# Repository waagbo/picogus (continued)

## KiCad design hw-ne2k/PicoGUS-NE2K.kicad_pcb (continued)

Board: 2 copper layers, 46 parts (0 on the bottom side), 94 nets, no tracks yet.

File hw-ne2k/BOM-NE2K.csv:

References,Qty,Value,Type,Footprint,Manufacturer,MPN,DigiKey PN,DigiKey link,DigiKey stock,Unit NOK (1 board),Line NOK (1 board),Alternatives,Notes
U1,1,Raspberry Pi Pico W,module (solder flat),RPi_PicoW_SMD_TH_USB,Raspberry Pi,SC0918,2648-SC0918CT-ND,https://www.digikey.no/no/products/result?keywords=2648-SC0918CT-ND,6986,72.90,72.90,Pico 2 W does NOT work (the NE2000 firmware is RP2040-only). Pico WH (pre-soldered headers) cannot be soldered flat.,Pico W (RP2040 + CYW43439 WiFi). Solder it FLAT (castellated edge or pins cut flush) so TP1-TP3 (USB) can be soldered from the back. Antenna end toward the bracket.
U2,1,74LVC244,SMD TSSOP-20,TSSOP-20_4.4x6.5mm_P0.65mm,Texas Instruments,SN74LVC244APW,296-26609-5-ND,https://www.digikey.no/no/products/result?keywords=296-26609-5-ND,2154,11.61,11.61,"Nexperia 74LVC244APW,118 (v1.2 BOM, DK 1727-2875-1-ND, 0 in stock today).","Octal buffer, 3V3, 5V-tolerant inputs"
"U3, U4",2,SN74CB3T3257,SMD TSSOP-16,TSSOP-16_4.4x5mm_P0.65mm,Texas Instruments,SN74CB3T3257PWR,296-17850-1-ND,https://www.digikey.no/no/products/result?keywords=296-17850-1-ND,4031,19.96,39.92,,TSSOP-16. No DIP or SOIC version exists (only PW/DGV).
U5,1,74AHC14,SMD SOIC-14,SOIC-14_3.9x8.7mm_P1.27mm,Diodes Inc,74AHC14S14-13,31-74AHC14S14-13CT-ND,https://www.digikey.no/no/products/result?keywords=31-74AHC1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,3070,3.55,3.55,,"Must be 74AHC14 (higher Schmitt threshold, see v1.2 changelog)."
U6,1,74LVC00,SMD SOIC-14,SOIC-14_3.9x8.7mm_P1.27mm,Diodes Inc,74LVC00AS14-13,31-74LVC00AS14-13CT-ND,https://www.digikey.no/no/products/result?keywords=31-74LVC0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,1816,3.65,3.65,,"Quad NAND, 3V3"
U7,1,74LVC1G00,SMD SOT-23-5,SOT-23-5,Texas Instruments,SN74LVC1G00DBVR,296-9845-1-ND,https://www.digikey.no/no/products/result?keywords=296-9845-1-ND,14500,1.34,1.34,,"Quad NAND, 3V3"
U8,1,APS6404L-3SQR-SN,SMD SOIC-8,SOIC-8_3.9x4.9mm_P1.27mm,AP Memory,APS6404L-3SQR-SN,1528-4677-ND,https://www.digikey.no/no/products/result?keywords=1528-4677-ND,4132,16.80,16.80,,SOIC-8. DigiKey does not stock the APS6404L itself; Adafruit 4677 is the DigiKey source (as in v1.2). Note: v1.2 BOM LCS
U10,1,74LVC2G06,SMD TSOP-6,TSOP-6_1.65x3.05mm_P0.95mm,Texas Instruments,SN74LVC2G06DBVR,296-13492-1-ND,https://www.digikey.no/no/products/result?keywords=296-13492-1-ND,25644,3.46,3.46,,"Open-drain inverters. U10A: IOCHRDY. U10B: unused (input driven by U5A, output open)."
U13,1,SST39SF010A,SMD PLCC-32,PLCC-32_11.4x14.0mm_P1.27mm,Microchip,SST39SF010A-70-4C-NHE,SST39SF010A-70-4C-NHE-ND,https://www.digikey.no/no/products/result?keywords=SST39SF01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,4137,18.87,18.87,,"Boot ROM: 128 KB 5 V flash = 4 banks of 32 KB, in-system writable from DOS (J2 fitted)"
U14,1,74HCT688,SMD SOIC-20W,SOIC-20W_7.5x12.8mm_P1.27mm,Texas Instruments,CD74HCT688M96,296-24357-1-ND,https://www.digikey.no/no/products/result?keywords=296-24357-1-ND,9672,7.43,7.43,,"Boot ROM address decoder (SA15-SA19 vs Pico-set base, enable)"
U15,1,74AHCT245,SMD TSSOP-20,TSSOP-20_4.4x6.5mm_P0.65mm,Texas Instruments,SN74AHCT245PWR,296-1118-1-ND,https://www.digikey.no/no/products/result?keywords=296-1118-1-ND,17137,7.72,7.72,,Boot ROM data buffer onto the ISA bus
U16,1,74AHCT1G08,SMD SOT-23-5,SOT-23-5,Texas Instruments,SN74AHCT1G08DBVR,296-1113-1-ND,https://www.digikey.no/no/products/result?keywords=296-1113-1-ND,66802,1.52,1.52,,~MEMSTB = ~SMEMR AND ~SMEMW (low during any memory cycle)
U17,1,USBLC6-2SC6,SMD SOT-23-6,SOT-23-6,STMicroelectronics,USBLC6-2SC6,497-5235-1-ND,https://www.digikey.no/no/products/result?keywords=497-5235-1-ND,144111,5.15,5.15,,USB ESD protection
D1,1,B5819W,SMD SOD-123,D_SOD-123,Slkor,B5819W,5399-B5819WCT-ND,https://www.digikey.no/no/products/result?keywords=5399-B5819WCT-ND,67294,2.69,2.69,,"1A 40V Schottky, DO-41"
F1,1,500mA PTC,SMD 1206,Fuse_1206_3216Metric,Bourns,MF-NSMF050-2,MF-NSMF050-2CT-ND,https://www.digikey.no/no/products/result?keywords=MF-NSMF05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,30039,3.81,3.81,,"USB VBUS polyfuse, 0.5 A hold"
"C1, C2",2,47uF,SMD 1206,C_1206_3216Metric,TDK,C3216X5R1A476M160AB,445-6006-1-ND,https://www.digikey.no/no/products/result?keywords=445-6006-1-ND,33669,7.97,15.94,v1.2 Samsung CL31A476MPHNNNE (0 at DigiKey today).,"47uF 35V aluminium electrolytic, 5mm dia, 2mm pitch"
"C3, C4, C5, C6, C7, C8, C9, C11, C12, C13, C14, C15, C17",13,0.1uF,SMD 0805,C_0805_2012Metric,Samsung,CL21B104KBCNNNC,1276-1003-1-ND,https://www.digikey.no/no/products/result?keywords=1276-1003-1-ND,4889645,0.43,5.59,,50V X7R.
C10,1,1uF,SMD 0805,C_0805_2012Metric,TDK,C2012X7R1H105K125AB,445-7547-1-ND,https://www.digikey.no/no/products/result?keywords=445-7547-1-ND,7594,2.88,2.88,,50V X7R.
C16,1,10uF,SMD 1206,C_1206_3216Metric,Samsung,CL31A106KAHNNNE,1276-1075-1-ND,https://www.digikey.no/no/products/result?keywords=1276-1075-1-ND,18634,2.11,2.11,"TDK C3216X5R1E106K160AB (DK 445-6862-1-ND, 43950).",USB VBUS bulk. 25V X5R. 1206 because no 10uF 0805 is in stock at DigiKey today.
R1,1,1k,SMD 0805,R_0805_2012Metric,Yageo,RC0805FR-071KL,311-1.00KCRCT-ND,https://www.digikey.no/no/products/result?keywords=311-1.00KCRCT-ND,732526,0.96,0.96,,1k 1/4W 1% metal film
"R2, R5, R6",3,15k,SMD 0805,R_0805_2012Metric,Yageo,RC0805FR-0715KL,311-15.0KCRCT-ND,https://www.digikey.no/no/products/result?keywords=311-15.0KCRCT-ND,127426,0.96,2.88,,15k 1/4W 1% metal film
"R3, R4",2,10k,SMD 0805,R_0805_2012Metric,Yageo,RC0805FR-0710KL,311-10.0KCRCT-ND,https://www.digikey.no/no/products/result?keywords=311-10.0KCRCT-ND,2120333,0.96,1.92,,10k 1/4W 1% metal film
J1,1,2x5 header,THT,PinHeader_2x05_P2.54mm_Vertical,Amphenol,10129381-910001BLF,10129381-910001BLF-ND,https://www.digikey.no/no/products/result?keywords=10129381-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,8685,6.96,6.96,,"IRQ select: one jumper (IRQ 2/9, 3, 4, 5 or 7)"
"J2, J6",2,1x2 header,THT,PinHeader_1x02_P2.54mm_Vertical,Amphenol,77311-118-02LF,609-4434-ND,https://www.digikey.no/no/products/result?keywords=609-4434-ND,56935,1.72,3.43,,J2: boot ROM write enable (fit the jumper only while flashing). J6: debug UART TX + GND. 30 uin gold.
J5,1,USB-A,THT,USB_A_Molex_67643_Horizontal,Molex,0676432910,WM11258-ND,https://www.digikey.no/no/products/result?keywords=WM11258-ND,894,18.20,18.20,"Wurth 614004134726 (DK 732-2731-ND, different footprint).","USB host port (mouse/joystick/storage), at the bracket below the antenna"
(jumpers),2,2.54mm jumper shunt,THT,,Harwin,M7582-05,952-2881-ND,https://www.digikey.no/no/products/result?keywords=952-2881-ND,,1.52,3.04,Blue: Harwin M7583-05 (DK 952-2882-ND). Red: Harwin M7581-05 (DK 952-2169-ND). Same open-top 2.54 mm shunt.,"One for J1 (IRQ), one for J2 (boot-ROM write enable: fit only while flashing the ROM)."
J3,0,,not fitted,,,,,,,,,,"ISA card edge (PCB gold fingers, order with chamfered/bevelled edge)"
H1,0,,not fitted,,,,,,,,,,Bracket mounting hole
H2,0,,not fitted,,,,,,,,,,Bracket mounting hole

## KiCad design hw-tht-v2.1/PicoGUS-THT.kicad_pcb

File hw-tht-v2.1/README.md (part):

# PicoGUS THT v2.1 – PicoGUS 2.0 in through hole, on a Waveshare Core2350B (RP2350B)

Board revision **v2.1**: the [PicoGUS 2.0](../hw-chipdown) circuit (chip-down RP2040, SMD) rebuilt for hand assembly
with through-hole parts. The RP2040, its flash, crystal and core regulator are replaced by a
**Waveshare Core2350B2** module (RP2350B, 16 MB flash, **8 MB PSRAM**) on four 2x8 sockets, and the module's PSRAM is
the GUS sample RAM, so v2.0's separate APS6404L is gone. Everything else is v2.0's circuit with the same GPIO map:
ISA bus logic, PCM5100A DAC, M62429 Waveblaster volume, MIDI out, USB-A host port and IRQ/DMA jumpers. The card is
the [THT v1.3.2](../hw-tht-v1.3.2/README.md) outline (102.0 × 99.95 mm), with v1.3.2's bracket-side connectors (USB-A,
line out, MIDI out) and bracket tab holes in v1.3.2's places, so the [v1.3.2 bracket](../hw-tht-v1.3.2/README.md#bracket) fits.
v2.0's passive line-out mix (four 1k resistors) is replaced by the **op-amp mixer of the THT v1.3 boards** (NE5532 on
ISA ±12 V, Waveblaster +6 dB), with film coupling capacitors and a DC-coupled DAC path.

The parts that only exist as SMD are soldered on the card: U1/U2 (SN74CB3T3257, TSSOP-16) and U10 (PCM5100A,
TSSOP-20) on THT v1.3.2's test-pad TSSOP footprints (hand-solder toes and a 0.7 mm test pad per pin), U13 (M62429L)
on v2.0's SOIC-8. Everything else is through hole; see
[Parts with no through-hole version](#parts-with-no-through-hole-version).

> **Status: schematic done; board placed and routed (4 layers, DRC clean, matches the schematic), for review. Not
> built or tested; no Gerbers yet. Firmware: ported and built (`picogus-v21.uf2`), not tested on hardware** (see
> [Firmware](#firmware) and [Layout status](#layout-status)).

Files:

| File | What |
|---|---|
| `PicoGUS-THT.kicad_pro/.kicad_sch/.kicad_pcb/.kicad_dru` | KiCad **10** project. Root sheet: v2.0's ISA logic, power, USB, Waveblaster and module |
| `audio.kicad_sch` | PCM5100A DAC sheet (v2.0's, footprints only) |
| `mixer.kicad_sch` | Line-out mixer: NE5532 inverting summing amplifier (from THT v1.3), ±12 V filters, Waveblaster input pull-downs |
| `PicoGUS-THT-schematic.pdf` | Schematic PDF |
| `BOM-THT.csv` | BOM with a **THT status** column (THT / THT but a different part than v2.0 / no THT version exists / module), the v2.0 part each line replaces, manufacturer, MPN, DigiKey and LCSC numbers, a digikey.no link, alternatives and digikey.no prices; then the kit items (module sockets and headers, jumpers), the optional IC sockets and the v2.0 parts that are gone |
| `BOM-THT-digikey-upload.csv` | DigiKey cart/BOM upload (see [Cost](#cost)). Customer Reference `PicoGUS-THT-2.1.x: <references>` on every line, so the bags of a mixed order say which board they are for; at most 48 characters (DigiKey prints "Character Limit Exceeded" instead of a longer one), so the 15 × 0.1 µF line reads `C2-7,14-16,20,…` |
| `BOM-THT-sockets.csv` (+ `-digikey-upload`) | Optional: every IC socketed, with socket and part heights against the Waveblaster daughterboard. The same parts are the optional socket lines of `BOM-THT.csv` |
| `BOM-THT-lcsc.csv`, `BOM-THT-lcsc-upload.csv`, `BOM-THT-sockets-lcsc-upload.csv` | The whole card from LCSC (see [Cost](#cost)): every BOM line with the LCSC part, order quantity (LCSC minimums), stock and price on the day and what to buy elsewhere; the uploads for LCSC's BOM tool, same customer references as the DigiKey ones |
| `tools/digikey_upload.py` | Writes both DigiKey upload files from `BOM-THT.csv` (`python3 tools/digikey_upload.py [cards]`; more than one card gives `-<n>x` files) |
| `tools/lcsc_bom.py` | Writes the three LCSC files from `BOM-THT.csv` with LCSC's live stock and prices (`python3 tools/lcsc_bom.py [cards]`) |
| `tools/gen_core2350b.py` | Generates the Core2350B footprint and 3D model in `hw-common` and checks the pin map |
| `PicoGUS-THT-top.png`, `PicoGUS-THT-bottom.png` | 3D renders |
| `docs/figures/routing.png` | The routed board: tracks per layer, vias and the AGND/AVDD islands |

The shared `PiGUS library` footprints are linked from `hw-common/`. **New in the shared library for v2.1:**
`Waveshare_Core2350B` (with a generated 3D model, `hw-common/parts/Waveshare_Core2350B.wrl`),
`USB_C_Receptacle_GCT_USB4085`, `TSSOP-16_4.4x5mm_P0.65mm_HandSolder_TestPads` and
`TSSOP-20_4.4x6.5mm_P0.65mm_HandSolder_TestPads` (THT v1.3.2's: KiCad's TSSOP with the toes to ±3.9 mm and one
0.7 mm round test pad per pin in two staggered columns per side, at x ±4.45 / ±5.1 mm),
`USB_A_Molex_67643_Horizontal_ShieldPin5` (KiCad's Molex 67643 with the shield pads
numbered 5, as the `USB_A` symbol's shield pin) and `DIP-8_W7.62mm_SOIC-8_Adapter` (no longer used here).

## What changed compared to v2.0

The schematic is v2.0's (`hw-chipdown`), upgraded to KiCad 10 and edited. Its netlist was compared with v2.0's
connection by connection: apart from the changes in this table the two are identical (119 multi-pin nets each).
Reference designators are v2.0's; new ones are D3, R19, R20 and C46.

| v2.0 | v2.1 | Why |
|---|---|---|
| U12 RP2040 (QFN-56), U11 W25Q128 flash, Y1 12 MHz crystal, R12/R14/R15/R16, C24–C37 (the RP2040 sheet) | **U12 Waveshare Core2350B** module on four 2x8 sockets (or soldered on its headers) | No chip-down RP2040 by hand. The module has the RP2350B, 16 MB flash, crystal, its own 3.3 V LDO and the 27 Ω USB resistors |
| U9 AMS1117-3.3 (SOT-223) | **U9 MCP1826S-3302E/AB** (TO-220) | Through hole, and 250 mV dropout: VSYS is now one Schottky drop below +5V (see [Power](#power)) |
| Q1 AO3401A ideal-diode switch (+5V → VSYS), R17 | **D3 1N5819** | No good TO-92 P-MOSFET; a second Schottky as for USB (D2) |
| J6 micro-USB (SMD) | **J6 GCT USB4085** through-hole USB-C + **R19/R20** 5.1 kΩ CC pull-downs | Through hole; device only, never sources VBUS |
| U6 74LVC2G06 (SOT-363), open-drain MIDI and I/O CH RDY drivers | **U6 74AHCT126** (DIP-14) on +5V + **C46** | No DIP open-drain inverter that runs on 3.3 V; the v1.3 THT boards' solution (OE = the old input, A tied low, so OE high pulls the line low). Spare gates tied low |
| U4/U5 74LVC00, U3 74AHC14, U7 SN74CB3T3245 (TSSOP) | 74AHC00 ×2, 74AHC14, **74AHC244** (DIP) | AHC: 3.3 V supply with 5 V tolerant inputs (as on v1.2/v1.3) |
| U1/U2 SN74CB3T3257, U10 PCM5100 (TSSOP) | same chips, **SMD on the card** (TSSOP-16/-20 on v1.3.2's hand-solder footprints with a test pad per pin) | No through-hole version exists |
| U8 APS6404L PSRAM (SOIC-8, GPIO0–3, PIO SPI) | **removed**: the Core2350B2's 8 MB PSRAM on the RP2350B's QMI (CS1 = GPIO47) | No through-hole PSRAM exists; the module's is memory mapped and faster. Needs the firmware port. GPIO0–3 are free |
| U13 M62429L (SOP-8) | same chip, **SMD on the card** (SOIC-8, v2.0's footprint) | The DIP-8 M62429P is not buyable |
| R6–R9 (1k passive mix), C43/C44 | **U11 NE5532 mixer** (sheet `mixer.kicad_sch`): R21–R32, C24–C29 | As THT v1.3: Waveblaster ×2 (+6 dB) and PCM ×1 summed, 100 Ω outputs, buffered line out |
| C39–C42 2.2 µF electrolytic (SMD) | **2.2 µF polyester film**, dual footprint (film on 5 mm, or a bipolar electrolytic on 2 mm) | Audio coupling: non-polar, low distortion |
| 0402/0603/0805/1206 R/C, CP_Elec_4x5.4, SOD-323, 0603 LED, 1206 PTC, 0805 beads, TL3305 switch, JST-SH debug | axial resistors and beads, radial MLCC discs and electrolytics, DO-41, 3 mm LED, radial PTC, 6 mm tactile switch, 1x3 header | Through hole |
| C11 47 µF (+3V3) | C11 10 µF | MCP1826S: at most 22 µF on its output |
| C38 100 µF ceramic | C38 100 µF electrolytic | Through hole |
| Card outline 102.87 × 96.74 mm, v2.0 bracket | **THT v1.3.2's outline** (102.0 × 99.95 mm) and bracket: J7 (MIDI out, top), J9 (line out) and J5 (USB-A, now v1.3.2's **Molex 67643**), H1/H2 and the ISA fingers at v1.3.2's positions | Reuses the v1.3.2 bracket; the 102 mm card is v1.3.2's cheaper JLCPCB size. The bracket's volume-pot hole is unused (v2.1's Waveblaster volume is digital) |
| 4 layers: In1 GND + AGND, In2 +3V3 + AVDD | 4 layers: In1.Cu GND plane + AGND island, In2.Cu +3V3 plane + AVDD island, under the audio section | As v2.0 |
| `+3.3V` power symbols | `+3V3` | The RP2040 sheet joined the two names; without it they would have split |

Unchanged references: J1 (ISA), J3 (IRQ/DMA), J7 (MIDI out), J8 (Waveblaster), J9 (line out), H1/H2, and every
GPIO assignment except GPIO0–3 (PSRAM, now free). Board positions: see [Layout status](#layout-status).

## Parts with no through-hole version

These are the v2.0 parts that cannot be replaced by a through-hole part. Everything else on v2.0 has a DIP, TO-220,
axial or radial equivalent (`THT status` column of `BOM-THT.csv`).

| v2.0 part | Package | Why there is no THT replacement | v2.1 |
|---|---|---|---|
| **RP2040** (+ W25Q128 flash, 12 MHz crystal) | QFN-56, SOIC-8, 3225 | No THT microcontroller of this class | **Waveshare Core2350B2 module** (RP2350B QFN-80 + 16 MB flash + crystal + 8 MB PSRAM) on four 2x8 headers |
| **APS6404L** 8 MB PSRAM | SOIC-8 | No THT PSRAM; the largest DIP SRAM (23LC1024) is 128 KB, a GUS needs 1 MB | **On the module**: the Core2350B2's PSRAM (firmware port needed) |
| **SN74CB3T3257** ×2 (5 V tolerant bus switches) | TSSOP-16 (no DIP/SOIC) | TI makes it in TSSOP/SSOP/TVSOP/VQFN only; the ISA interface needs it | Same chip, **SMD on the card** (TSSOP-16, 0.65 mm pitch) |
| **PCM5100A** DAC | TSSOP-20 only | The whole PCM510x family is TSSOP-20 | Same chip, **SMD on the card** (TSSOP-20, 0.65 mm pitch) |
| **M62429** volume control | SOP-8 (DIP-8 M62429P discontinued) | No DIP part in stock at DigiKey or LCSC; DIP clones (FM62429, U2429) only at hobby shops | Same chip, **SMD on the card** (SOIC-8, 1.27 mm pitch) |
| micro-USB receptacle | SMD | – | **GCT USB4085** through-hole USB-C: through hole, but 0.85 mm contact pitch (the hardest joint on the card) |

Replaced by a different through-hole part (circuit change): 74LVC2G06 → **74AHCT126** (U6), AO3401A → **1N5819**
(D3), AMS1117 → **MCP1826S** (U9), 74LVC00 → 74AHC00, SN74CB3T3245/74LVC244 → 74AHC244.

## Cost

digikey.no prices of 2026-10-30, for one board, in NOK; shipping not included. Per-line prices are in `BOM-THT.csv`.

| | NOK excl. MVA | NOK incl. 25 % MVA |
|---|---|---|
| DigiKey order, `BOM-THT-digikey-upload.csv` (43 lines) | 580.00 | 725.00 |
| Optional IC sockets, `BOM-THT-sockets-digikey-upload.csv` (U3–U7, U11) | 58.98 | 73.72 |
| Both | 638.98 | 798.73 |

* **Not in the DigiKey order**: the Core2350B2 (waveshare.com, US$6.99) and the M62429L (LCSC C52260216, minimum 5),
  and the PCB.
* J5 is now v1.3.2's Molex 67643 (DK WM4993-ND, 16.58 NOK, price of 2026-10-31), so it is in the DigiKey order.
* **C39–C42** (2.2 µF film, 61 NOK) are on backorder at DigiKey until about April 2027: see the LCSC film part or the
  bipolar electrolytic in [Audio](#audio).

**LCSC instead** (lcsc.com prices and stock of 2026-11-06, US$, shipping not included; `BOM-THT-lcsc.csv` has every
line):

| | US$ |
|---|---|
| LCSC order, `BOM-THT-lcsc-upload.csv` (40 lines, quantities raised to LCSC's minimums) | 50.93 |
| Optional IC sockets, `BOM-THT-sockets-lcsc-upload.csv` | 7.24 |

* **Not at LCSC**: U3 SN74AHC14N, U6 SN74AHCT126N and U9 MCP1826S-3302E/AB (none in stock, and no LCSC part fits
  without a design change: the 74HC14 does not take 5 V inputs at 3.3 V, the 125 has the opposite enable, the
  LM2940 clones want a larger output capacitor with ESR): buy them at DigiKey (296-4550-5-ND, 296-4659-5-ND,
  MCP1826S-3302E/AB-ND, about 30 NOK). The Core2350B2 comes from Waveshare.
* **Different parts from the BOM** (all in the `Note` column): U7 is TI's SN74LVC244AN (same pinout, 5 V-tolerant
  inputs at 3.3 V like the AHC244, stronger outputs), J7/J9 the XKB clones of the CUI jacks (as on THT v1.3.2),
  C21/C22 Dersonic C0G discs, R27/R28 and R31/R32 the taped Yageo MFR-25, and the generic headers, sockets,
  ferrites, film and electrolytic capacitors named in `BOM-THT.csv`.
* U4/U5 (SN74AHC00N): 60 in stock at LCSC on the day, at US$1.46 each.

## Audio

* **DAC**: PCM5100A (U10) as v2.0, output RC filter R10/R11 470 Ω + **C0G** C21/C22 2.2 nF (polypropylene film
  WIMA FKP2 is the alternative). Charge pump and decoupling MLCCs per the TI datasheet (X7R).
* **Waveblaster volume**: M62429L (U13) on AVDD as v2.0, inputs pulled to AGND by 100k (R31/R32, as THT v1.3),
  **film** coupling capacitors in and out (C39–C42).
* **Mixer** (`mixer.kicad_sch`, THT v1.3's): U11 NE5532 inverting summing amplifier on ISA ±12 V through 10 Ω / 47 µF
  (R29/R30, C28/C29). Waveblaster through 10k (×2, +6 dB), PCM through 20k (×1), feedback 20k ‖ 47 pF C0G (pole about
  170 kHz), 100 Ω output resistors to the jack. The PCM5100A's output is ground centred, so the PCM path is DC coupled:
  no electrolytic anywhere in the PCM path. U11 can be socketed for an OPA2134PA.
* **Capacitor choices** (`Alternatives` column of the BOM): 2.2 µF film at 5 mm pitch is scarce: DigiKey had none in
  stock on 2026-10-29 (TDK B32529D0225J000 on backorder), LCSC has Faratronic C241J225J2SC000. The footprint also
  takes a 5 mm bipolar electrolytic (Rubycon 50NXA2R2MEFC5X11, in stock) on its inner holes. Nichicon's Muse ES/BP, FG
  and FW are discontinued in 5 mm cans, so AVDD bulk C38 is a Panasonic FR (EEU-FR1C101).

* **Ground and supply planes**: as on v2.0, AGND (In1.Cu) and AVDD (In2.Cu) are copper islands cut out of the GND and
  +3V3 planes under the audio section (x 140–209.6, y 47.5–81.7, see `docs/figures/routing.png`): the DAC's analog
  pin row and output filter, the volume control, the film capacitors, the mixer and the line-out jack. They meet GND
  and +3V3 only at FB3 and FB4, side by side across the island's lower left edge. The Waveblaster header, the MIDI
  jack and the DAC's digital row stay outside them. Digital tracks cross the islands only where they must: the volume
  control's clock and data (about 18 and 14 mm, to U13 on the island), MIDI (about 45 mm of UART_TX to the
  Waveblaster and the MIDI resistors, and 16 mm from R2 to J7: both are beyond the island), 13 mm of RI/OCHRDY and 4
  mm of DIN. The ±12 V supplies of the mixer and the +5 V of the USB-A port also run over them.

## Core2350B module

The Core2350B is 25.4 × 25.4 mm with 64 plated holes on a 2.54 mm grid: a 10×10 outer ring and an 8×8 inner
ring. Waveshare's schematic draws them as four 2x8 headers, P1–P4, arranged as a pinwheel, so **four standard 2x8
female headers** take the module (BOM lines `(U12 socket)` and `(U12 headers)`). The footprint numbers the pads
16·(header − 1) + pin. Seen from the top, pin 1 of each header is a GND corner; the module's chamfered corner
(pad 1, P1.1) is at the top left:

```
  G   0  VB  3E RUN UDP UDM  BS  47   G      VB  VBUS (module LDO input)      3E  3V3_EN (100k up to VBUS)
  2   1 3V3   G  AV  SC   G  SD  46  45      3V3 module LDO output            AV  ADC_VREF
  4   3                          43  44      UDP/UDM  USB D+/D- (27R inside)  SC/SD  SWCLK/SWDIO
  6   5                          41  42      BS  BOOTSEL                      G   GND
  8   7                          39  40      numbers: GPIO
 10   9                          37  38
 12  11                          35  36      P1 = left two columns (GPIO0-14)
 14  13                          33  34      P2 = top two rows (USB, SWD, RUN, BOOTSEL, power, GPIO45-47)
 15  16  18  20  22  24  26  28  31  32      P3 = bottom two rows (GPIO15-29)
  G  17  19  21  23  25  27  29  30   G      P4 = right two columns (GPIO30-44)
```

Source: Waveshare's [Core2350B schematic](https://files.waveshare.com/wiki/Core2350B0/Core2350B.pdf) (P1–P4) and
[pinout drawing](https://www.waveshare.com/wiki/Core2350B0); `tools/gen_core2350b.py` checks that every GPIO
appears once and that the cells form the two rings. On the module: the user LED is on **GPIO39**, and on the
Core2350B1/B2 the PSRAM chip select (QMI CS1) is **GPIO47** (through a 0 Ω link to the edge pin).

* **U12 is placed at 0°**: GPIO0–14 (P1) face the logic on the left, GPIO15–29 (P3) face the ISA fingers,
  USB/SWD/RUN/BOOTSEL/power (P2) face up and the unused GPIO30–44 (P4) face the bracket.
* **Variants**: Core2350B0 (no PSRAM, $4.99), B1 (2 MB, $5.99), **B2 (8 MB, $6.99, recommended)**; the `-Kit`
  versions add Waveshare's USB-C FPC adapter. Not sold by DigiKey: buy from waveshare.com (SKU 31690 for the B2) or a
  Waveshare reseller.
* **Heights**: on 8.5 mm female headers the module's top is at about 12 mm. It sits right of the Waveblaster
  daughterboard area, so that is fine. Soldered straight into the card on its male headers, the module sits at about
  3.5 mm.

## GPIO map (= v2.0)

| GPIO | Net | GPIO | Net |
|---|---|---|---|
| 0–3 | free (v2.0: U8 PSRAM; the GUS RAM is the module's PSRAM now) | 16 | DIN (I2S to U10) |
| | | 17 | BCK |
| | | 18 | LRCK |
| | | 19 | ~RDACK |
| 4 | ~RIOW | 20 | RTC |
| 5 | ~RIOR | 21 | RIRQ |
| 6–13 | AD0–AD7 (U1/U2 bus switches) | 22 | RDRQ |
| 14 | RA8 | 23 | LED (D1) |
| 15 | RA9 | 24, 25 | RV_DATA, RV_CLK (U13 M62429) |
| 26 | RI/OCHRDY (U6) | 27 | ADS (U1/U2 select, U3) |
| 28 | UART_TX (MIDI, J4, Waveblaster) | 29 | GND (board ID, as v2.0) |
| 30–46 | not connected (39: module LED) | 47 | module PSRAM CS (QMI CS1), on the module |

## Power

* **VSYS** = +5V (ISA) through **D3** or USB VBUS (J6) through **D2**, both 1N5819 (as the Pico's VSYS). This
  replaces v2.0's AO3401A ideal diode: VSYS is about 0.3–0.4 V below +5V.
* **U9 MCP1826S-3302E/AB** (TO-220, 1 A, 250 mV dropout, **lying down, tab down**: `TO-220-3_Horizontal_TabDown`,
  so it stays well under the Waveblaster daughterboard) makes the card's +3V3 from VSYS: logic, bus switches,
  DAC (AVDD through FB4) and M62429. With an AMS1117-class regulator (about 1.1 V dropout) a low ISA +5V would
  not leave enough headroom after the diode. Its pinout is VIN–GND–VOUT, tab GND (**not** the 1117 pinout, so an
  LD1117V33 does not fit). C11/C13 (10 µF) + C10 (1 µF) on its output: Microchip asks for at least 1 µF and at most
  22 µF. C12 (10 µF, input) is about 10 mm from the VIN pin, joined by a 0.4 mm track.
* **The module powers itself**: VSYS goes to the module's **VBUS** pin, and its own LDO (ME6217C33, 800 mA, 3V3_EN
  pulled up on the module) makes the module's 3.3 V. The module's **3V3 pin is not connected**: the ME6217 must not
  see VOUT above VIN + 0.3 V, so it cannot be back-fed from U9. Both rails are 3.3 V ± 2 %; the RP2350's GPIO0–39 are
  5 V tolerant while it is powered and 3.3 V failsafe when it is not.
* The module's own FPC USB port (the `-Kit` adapter) also works for programming: its VBUS powers the module, and
  through the module's VBUS pin also VSYS and U9 (D2/D3 keep it off the ISA +5V and J6).
* **Reset (RUN)**: as on v2.0, ISA RESET DRV reaches the module's RUN pin through U5 (pin 8), so a PC reset also
  resets the RP2350, and RUN goes back into U5 (pin 5) so that a reset also clears BUSOE. U5 pin 8 now drives RUN
  **through R4 (1 kΩ in series)** instead of v2.0's pull-up, so the **RUN button SW2** (6 × 6 mm, next to BOOTSEL SW1)
  can pull RUN to GND without shorting the gate output (3.3 mA while pressed). C45 (0.1 µF) on RUN filters it. To
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
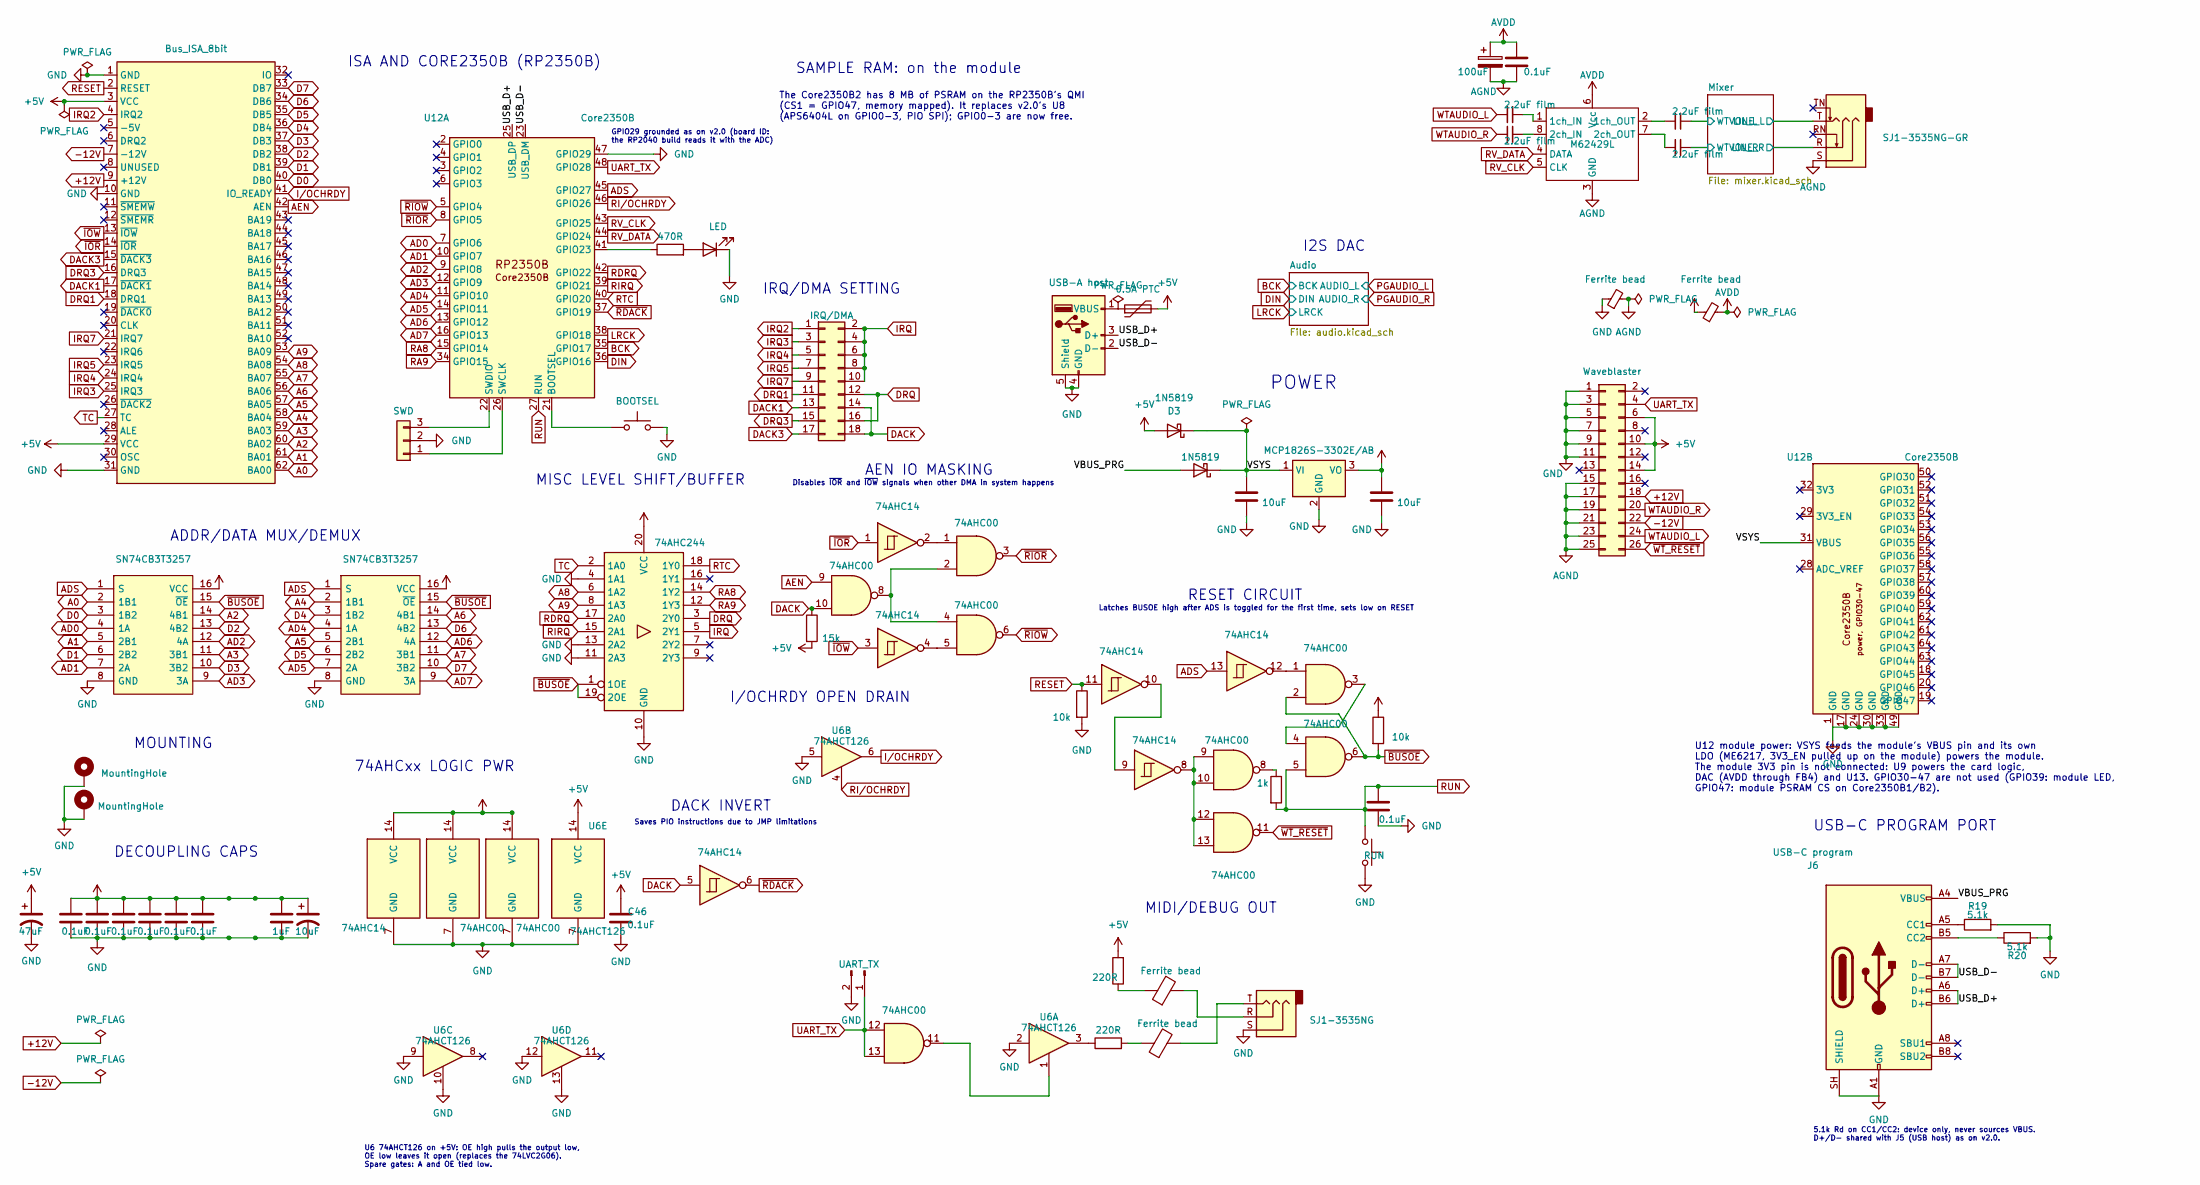
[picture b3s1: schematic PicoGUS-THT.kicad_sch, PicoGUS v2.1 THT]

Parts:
C1: 47uF; CP_Radial_D5.0mm_P2.00mm; MPN 35YXJ47M5X11; DigiKey 1189-2919-ND
C2, C3, C4, C5, C6, C7, C23, C45, C46: 0.1uF; C_Disc_D5.0mm_W2.5mm_P5.00mm; MPN RDER71H104K0M1H03A; DigiKey 490-9144-1-ND
C10: 1uF; C_Disc_D5.0mm_W2.5mm_P5.00mm; MPN RDER71H105K2M1H03A; DigiKey 490-9146-1-ND
C11, C12, C13: 10uF; C_Disc_D5.0mm_W2.5mm_P5.00mm; MPN RCER71H106MWM1H03A; DigiKey 490-7518-1-ND
C38: 100uF; CP_Radial_D5.0mm_P2.00mm; MPN EEU-FR1C101; DigiKey P14391-ND
C39, C40, C41, C42: 2.2uF film; C_Film_P5.00mm_7.8x7.8mm_or_CP_D5.0mm_P2.00mm; MPN B32529D0225J000; DigiKey 495-1127-ND
D1: LED; LED_D3.0mm; MPN LTL-4231N; DigiKey 160-1142-ND
D2, D3: 1N5819; D_DO-41_SOD81_P10.16mm_Horizontal; MPN 1N5819RLG; DigiKey 1N5819RLGOSCT-ND
F1: 0.5A PTC; Fuse_Bourns_MF-RHT050; MPN MF-R050; DigiKey MF-R050-ND
FB1, FB2, FB3, FB4: Ferrite bead; R_Axial_DIN0309_L9.0mm_D3.2mm_P12.70mm_Horizontal; MPN 2743002112; DigiKey 1934-1477-1-ND
H1, H2: MountingHole; MountingHole_3.2mm_M3_Pad
J1: Bus_ISA_8bit; BUS_PC_chamfer
J2: SWD; PinHeader_1x03_P2.54mm_Vertical; MPN PREC040SAAN-RC; DigiKey S1012EC-40-ND
J3: IRQ/DMA; PinHeader_2x09_P2.54mm_Vertical; MPN 10129381-918001BLF; DigiKey 609-10129381-918001BLF-ND
J4: UART_TX; PinHeader_1x02_P2.54mm_Vertical; MPN PREC040SAAN-RC; DigiKey S1012EC-40-ND
J5: USB-A host; USB_A_Molex_67643_Horizontal_ShieldPin5; MPN 0676430910; DigiKey WM4993-ND
J6: USB-C program; USB_C_Receptacle_GCT_USB4085; MPN USB4085-GF-A; DigiKey 2073-USB4085-GF-ACT-ND
J7: SJ1-3535NG; Jack_3.5mm_CUI_SJ1-3535NG_Horizontal; MPN SJ1-3535NG; DigiKey CP1-3535NG-ND
J8: Waveblaster; Wavetable_NoMountingHoles; MPN PEC13DAAN; DigiKey 35-PEC13DAAN-ND
J9: SJ1-3535NG-GR; Jack_3.5mm_CUI_SJ1-3535NG_Horizontal; MPN SJ1-3535NG-GR; DigiKey CP1-3535NG-GR-ND
R1, R5: 10k; R_Axial_DIN0207_L6.3mm_D2.5mm_P10.16mm_Horizontal; MPN MFR-25FBF52-10K; DigiKey 10.0KXBK-ND
R2, R3: 220R; R_Axial_DIN0207_L6.3mm_D2.5mm_P10.16mm_Horizontal; MPN RNMF14FTC220R; DigiKey S220CACT-ND
R4: 1k; R_Axial_DIN0207_L6.3mm_D2.5mm_P10.16mm_Horizontal; MPN MFR-25FBF52-1K; DigiKey 1.00KXBK-ND
R13: 470R; R_Axial_DIN0207_L6.3mm_D2.5mm_P10.16mm_Horizontal; MPN RNMF14FTC470R; DigiKey S470CACT-ND
R18: 15k; R_Axial_DIN0207_L6.3mm_D2.5mm_P10.16mm_Horizontal; MPN MFR-25FBF52-15K; DigiKey 15.0KXBK-ND
R19, R20: 5.1k; R_Axial_DIN0207_L6.3mm_D2.5mm_P10.16mm_Horizontal; MPN MFR-25FBF52-5K1; DigiKey MFR-25FBF52-5K1-ND
SW1: BOOTSEL; SW_PUSH_6mm; MPN 1825910-6; DigiKey 450-1650-ND
SW2: RUN; SW_PUSH_6mm; MPN 1825910-6; DigiKey 450-1650-ND
U1, U2: SN74CB3T3257; TSSOP-16_4.4x5mm_P0.65mm_HandSolder_TestPads; Manufacturer_Part_Number 74FST3257DR2G; Mouser Part Number 863-74FST3257DR2G
U3: 74AHC14; DIP-14_W7.62mm; MPN SN74AHC14N; DigiKey 296-4550-5-ND
U4, U5: 74AHC00; DIP-14_W7.62mm; MPN SN74AHC00N; DigiKey 296-4510-5-ND
U6: 74AHCT126; DIP-14_W7.62mm; MPN SN74AHCT126N; DigiKey 296-4659-5-ND
U7: 74AHC244; DIP-20_W7.62mm; MPN SN74AHC244N; DigiKey 296-4585-5-ND
U9: MCP1826S-3302E/AB; TO-220-3_Horizontal_TabDown; MPN MCP1826S-3302E/AB; DigiKey MCP1826S-3302E/AB-ND
U12: Core2350B; Waveshare_Core2350B; MPN Core2350B2; DigiKey not stocked: waveshare.com SKU 31690 (B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
U13: M62429L; SOIC-8_3.9x4.9mm_P1.27mm; MPN M62429L.TR; DigiKey not stocked: LCSC only (DigiKey marketp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

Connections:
+3V3: C2.1, C3.1, C4.1, C5.1, C6.1, C7.1, C10.1, C11.1, C13.1, FB4.1, R5.1, U1.16 (VCC), U2.16 (VCC), U3.14 (VCC), U4.14 (VCC), U5.14 (VCC), U7.20 (VCC), U9.3 (VO); also elsewhere on the board
+5V: C1.1, C46.1, D3.2 (A), F1.2, J1.3 (VCC), J1.29 (VCC), J8.6, J8.10, J8.14, R3.2, R18.2, U6.14 (VCC)
+12V: J1.9 (+12V), J8.18; also elsewhere on the board
-12V: J1.7 (-12V), J8.22; also elsewhere on the board
/Mixer/LINE_L: J9.T; also elsewhere on the board
/Mixer/LINE_R: J9.R; also elsewhere on the board
/Mixer/WTVOL_L: C41.2; also elsewhere on the board
/Mixer/WTVOL_R: C42.2; also elsewhere on the board
/USB_D+: J5.3 (D+), J6.A6 (D+), J6.B6 (D+), U12.25 (USB_DP)
/USB_D-: J5.2 (D-), J6.A7 (D-), J6.B7 (D-), U12.23 (USB_DM)
/VBUS_PRG: D2.2 (A), J6.A4 (VBUS), J6.A9 (VBUS), J6.B4 (VBUS), J6.B9 (VBUS)
/VSYS: C12.1, D2.1 (K), D3.1 (K), U9.1 (VI), U12.31 (VBUS)
A0: J1.62 (BA00), U1.2 (1B1)
A1: J1.61 (BA01), U1.5 (2B1)
A2: J1.60 (BA02), U1.14 (4B1)
A3: J1.59 (BA03), U1.11 (3B1)
A4: J1.58 (BA04), U2.2 (1B1)
A5: J1.57 (BA05), U2.5 (2B1)
A6: J1.56 (BA06), U2.14 (4B1)
A7: J1.55 (BA07), U2.11 (3B1)
A8: J1.54 (BA08), U7.6 (1A2)
A9: J1.53 (BA09), U7.8 (1A3)
AD0: U1.4 (1A), U12.7 (GP6)
AD1: U1.7 (2A), U12.10 (GP7)
AD2: U1.12 (4A), U12.9 (GP8)
AD3: U1.9 (3A), U12.12 (GP9)
AD4: U2.4 (1A), U12.11 (GP10)
AD5: U2.7 (2A), U12.14 (GP11)
AD6: U2.12 (4A), U12.13 (GP12)
AD7: U2.9 (3A), U12.16 (GP13)
ADS: U1.1 (S), U2.1 (S), U3.13, U12.45 (GP27)
AEN: J1.42 (AEN), U4.9
AGND: C23.2, C38.2, FB3.2, J8.15, J8.17, J8.19, J8.21, J8.23, J8.25, J9.S, U13.3 (GND); also elsewhere on the board
AVDD: C23.1, C38.1, FB4.2, U13.6 (Vcc); also elsewhere on the board
BCK: U12.35 (GP17); also elsewhere on the board
D0: J1.40 (DB0), U1.3 (1B2)
D1: J1.39 (DB1), U1.6 (2B2)
D2: J1.38 (DB2), U1.13 (4B2)
D3: J1.37 (DB3), U1.10 (3B2)
D4: J1.36 (DB4), U2.3 (1B2)
D5: J1.35 (DB5), U2.6 (2B2)
D6: J1.34 (DB6), U2.13 (4B2)
D7: J1.33 (DB7), U2.10 (3B2)
DACK: J3.14, J3.18, R18.1, U3.5, U4.10
DACK1: J1.17 (~DACK1), J3.13
DACK3: J1.15 (~DACK3), J3.17
DIN: U12.36 (GP16); also elsewhere on the board
DRQ: J3.12, J3.16, U7.3 (2Y0)
DRQ1: J1.18 (DRQ1), J3.11
DRQ3: J1.16 (DRQ3), J3.15
GND: C1.2, C2.2, C3.2, C4.2, C5.2, C6.2, C7.2, C10.2, C11.2, C12.2, C13.2, C45.2, C46.2, D1.1 (K), FB3.1, H1.1, H2.1, J1.1 (GND), J1.10 (GND), J1.31 (GND), J2.2, J4.2, J5.4 (GND), J5.5 (Shield), J6.A1 (GND), J6.A12 (GND), J6.B1 (GND), J6.B12 (GND), J6.SH (SHIELD), J7.S, J8.1, J8.3, J8.5, J8.7, J8.9, J8.11, R1.2, R19.2, R20.2, SW1.2, SW2.2, U1.8 (GND), U2.8 (GND), U3.7 (GND), U4.7 (GND), U5.7 (GND), U6.2, U6.5, U6.7 (GND), U6.9, U6.10, U6.12, U6.13, U7.4 (1A1), U7.10 (GND), U7.11 (2A3), U7.13 (2A2), U9.2 (GND), U12.1 (GND), U12.17 (GND), U12.24 (GND), U12.30 (GND), U12.33 (GND), U12.47 (GP29), U12.49 (GND); also elsewhere on the board
IRQ: J3.2, J3.4, J3.6, J3.8, J3.10, U7.5 (2Y1)
IRQ2: J1.4 (IRQ2), J3.1
IRQ3: J1.25 (IRQ3), J3.3
IRQ4: J1.24 (IRQ4), J3.5
IRQ5: J1.23 (IRQ5), J3.7
IRQ7: J1.21 (IRQ7), J3.9
I/OCHRDY: J1.41 (IO_READY), U6.6
LRCK: U12.38 (GP18); also elsewhere on the board
unnamed: D1.2 (A), R13.2
unnamed: FB1.1, R2.2
unnamed: FB1.2, J7.T
unnamed: FB2.1, R3.1
unnamed: FB2.2, J7.R
unnamed: J2.1, U12.26 (SWCLK)
unnamed: J2.3, U12.22 (SWDIO)
unnamed: F1.1, J5.1 (VBUS)
unnamed: J6.A5 (CC1), R19.1
unnamed: J6.B5 (CC2), R20.1
unnamed: R2.1, U6.3
unnamed: R4.1, U5.8
unnamed: U3.2, U4.1
unnamed: U3.4, U4.5
unnamed: U3.8, U5.9, U5.10, U5.12, U5.13
unnamed: U3.9, U3.10
unnamed: U3.12, U5.1
unnamed: U4.2, U4.4, U4.8
unnamed: U4.11, U6.1
unnamed: U5.3, U5.4
unnamed: SW1.1, U12.21 (BOOTSEL)
unnamed: R13.1, U12.41 (GP23)
unnamed: C39.2, U13.1 (1ch_IN)
unnamed: C41.1, U13.2 (1ch_OUT)
unnamed: C40.2, U13.8 (2ch_IN)
unnamed: C42.1, U13.7 (2ch_OUT)
RA8: U7.14 (1Y2), U12.15 (GP14)
RA9: U7.12 (1Y3), U12.34 (GP15)
RDRQ: U7.17 (2A0), U12.42 (GP22)
RESET: J1.2 (RESET), R1.1, U3.11
RIRQ: U7.15 (2A1), U12.39 (GP21)
RI/OCHRDY: U6.4, U12.46 (GP26)
RTC: U7.18 (1Y0), U12.40 (GP20)
RUN: C45.1, R4.2, SW2.1, U5.5, U12.27 (RUN)
RV_CLK: U12.43 (GP25), U13.5 (CLK)
RV_DATA: U12.44 (GP24), U13.4 (DATA)
TC: J1.27 (TC), U7.2 (1A0)
UART_TX: J4.1, J8.4, U4.12, U4.13, U12.48 (GP28)
WTAUDIO_L: C39.1, J8.24; also elsewhere on the board
WTAUDIO_R: C40.1, J8.20; also elsewhere on the board
~BUSOE: R5.2, U1.15 (~OE), U2.15 (~OE), U5.2, U5.6, U7.1 (1OE), U7.19 (2OE)
~IOR: J1.14 (~IOR), U3.1
~IOW: J1.13 (~IOW), U3.3
~RDACK: U3.6, U12.37 (GP19)
~RIOR: U4.3, U12.8 (GP5)
~RIOW: U4.6, U12.5 (GP4)
~WT_RESET: J8.26, U5.11

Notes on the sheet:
Saves PIO instructions due to JMP limitations
5.1k Rd on CC1/CC2: device only, never sources VBUS. D+/D- shared with J5 (USB host) as on v2.0.
U6 74AHCT126 on +5V: OE high pulls the output low, OE low leaves it open (replaces the 74LVC2G06). Spare gates: A and OE tied low.
DECOUPLING CAPS
GPIO29 grounded as on v2.0 (board ID: the RP2040 build reads it with the ADC)
I2S DAC
USB-C PROGRAM PORT
Disables ~{IOR} and ~{IOW} signals when other DMA in system happens
Latches BUSOE high after ADS is toggled for the first time, sets low on RESET
MIDI/DEBUG OUT
MOUNTING
MISC LEVEL SHIFT/BUFFER
IRQ/DMA SETTING
U12 module power: VSYS feeds the module's VBUS pin and its own LDO (ME6217, 3V3_EN pulled up on the module) powers the module. The module 3V3 pin is not connected: U9 powers the card logic, DAC (AVDD through FB4) and U13. GPIO30-47 are not used (GPIO39: module LED, GPIO47: module PSRAM CS on Core23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
DACK INVERT
ADDR/DATA MUX/DEMUX
SAMPLE RAM: on the module
The Core2350B2 has 8 MB of PSRAM on the RP2350B's QMI (CS1 = GPIO47, memory mapped). It replaces v2.0's U8 (APS6404L on GPIO0-3, PIO SPI); GPIO0-3 are now free.
AEN IO MASKING
ISA AND CORE2350B (RP2350B)
POWER
RESET CIRCUIT
I/OCHRDY OPEN DRAIN
74AHCxx LOGIC PWR

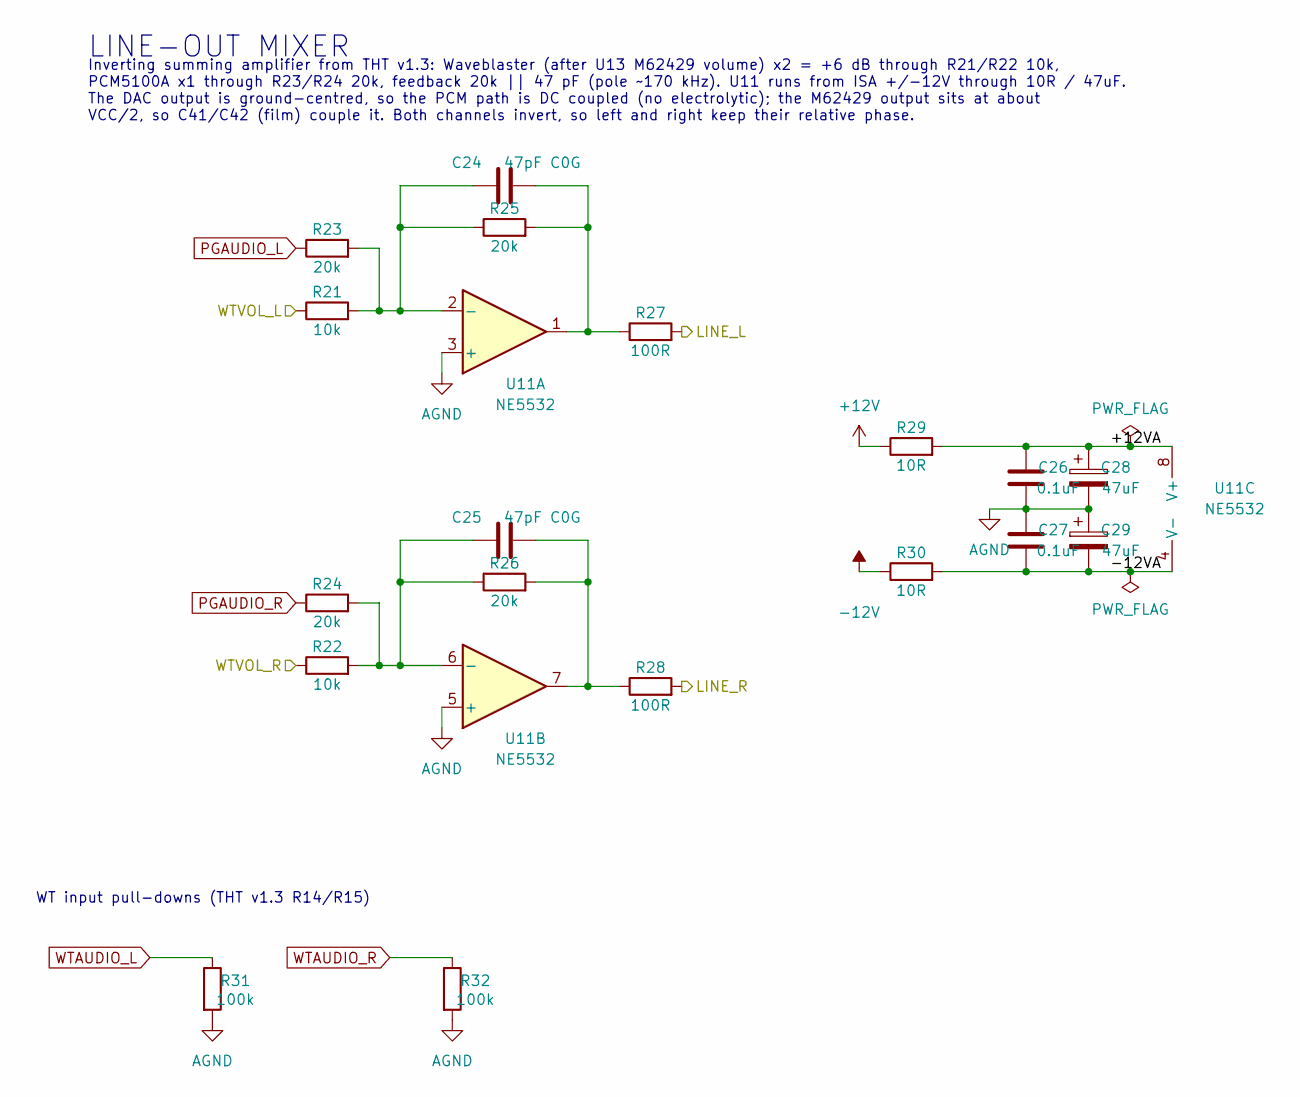
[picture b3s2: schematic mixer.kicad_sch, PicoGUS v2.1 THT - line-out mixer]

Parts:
C24, C25: 47pF C0G; C_Disc_D5.0mm_W2.5mm_P5.00mm; MPN K470J15C0GF5TH5; DigiKey BC1038CT-ND
C26, C27: 0.1uF; C_Disc_D5.0mm_W2.5mm_P5.00mm; MPN RDER71H104K0M1H03A; DigiKey 490-9144-1-ND
C28, C29: 47uF; CP_Radial_D5.0mm_P2.00mm; MPN 35YXJ47M5X11; DigiKey 1189-2919-ND
R21, R22: 10k; R_Axial_DIN0207_L6.3mm_D2.5mm_P10.16mm_Horizontal; MPN MFR-25FBF52-10K; DigiKey 10.0KXBK-ND
R23, R24, R25, R26: 20k; R_Axial_DIN0207_L6.3mm_D2.5mm_P10.16mm_Horizontal; MPN MFR-25FBF52-20K; DigiKey 20.0KXBK-ND
R27, R28: 100R; R_Axial_DIN0207_L6.3mm_D2.5mm_P10.16mm_Horizontal; MPN MFR-25FBF52-100R; DigiKey 100XBK-ND
R29, R30: 10R; R_Axial_DIN0207_L6.3mm_D2.5mm_P10.16mm_Horizontal; MPN MFR-25FBF52-10R; DigiKey 10.0XBK-ND
R31, R32: 100k; R_Axial_DIN0207_L6.3mm_D2.5mm_P10.16mm_Horizontal; MPN MFR-25FBF52-100K; DigiKey 100KXBK-ND
U11: NE5532; DIP-8_W7.62mm; MPN NE5532P; DigiKey 296-1410-5-ND

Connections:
+12V: R29.1; also elsewhere on the board
-12V: R30.1; also elsewhere on the board
/Mixer/+12VA: C26.1, C28.1, R29.2, U11.8 (V+)
/Mixer/-12VA: C27.2, C29.2, R30.2, U11.4 (V-)
/Mixer/LINE_L: R27.2; also elsewhere on the board
/Mixer/LINE_R: R28.2; also elsewhere on the board
/Mixer/WTVOL_L: R21.1; also elsewhere on the board
/Mixer/WTVOL_R: R22.1; also elsewhere on the board
AGND: C26.2, C27.1, C28.2, C29.1, R31.2, R32.2, U11.3 (+), U11.5 (+); also elsewhere on the board
unnamed: C24.2, R25.2, R27.1, U11.1
unnamed: C25.2, R26.2, R28.1, U11.7
unnamed: C24.1, R21.2, R23.2, R25.1, U11.2 (-)
unnamed: C25.1, R22.2, R24.2, R26.1, U11.6 (-)
PGAUDIO_L: R23.1; also elsewhere on the board
PGAUDIO_R: R24.1; also elsewhere on the board
WTAUDIO_L: R31.1; also elsewhere on the board
WTAUDIO_R: R32.1; also elsewhere on the board

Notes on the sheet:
LINE-OUT MIXER
Inverting summing amplifier from THT v1.3: Waveblaster (after U13 M62429 volume) x2 = +6 dB through R21/R22 10k, PCM5100A x1 through R23/R24 20k, feedback 20k || 47 pF (pole ~170 kHz). U11 runs from ISA +/-12V through 10R / 47uF. The DAC output is ground-centred, so the PCM path is DC coupled (no e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
WT input pull-downs (THT v1.3 R14/R15)

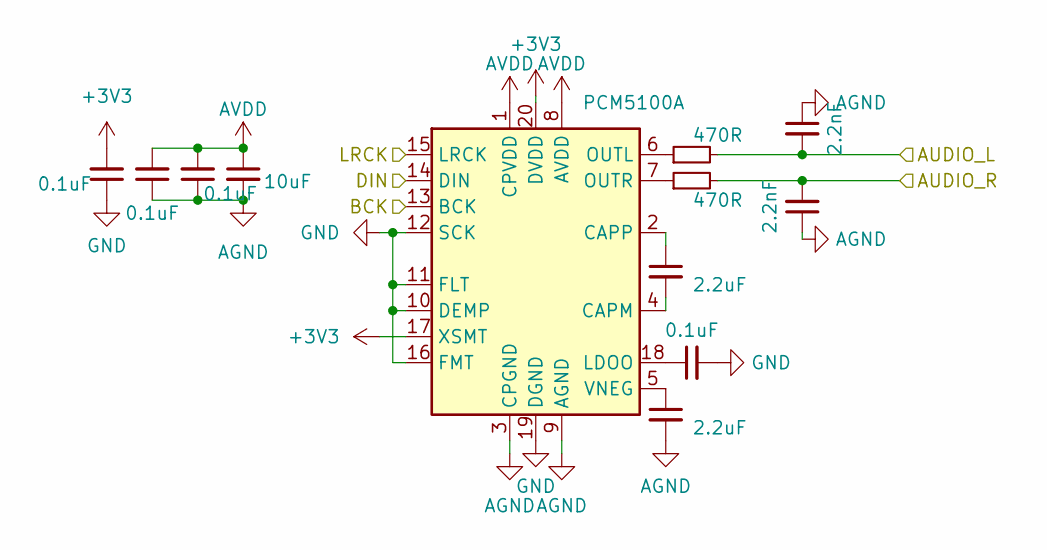
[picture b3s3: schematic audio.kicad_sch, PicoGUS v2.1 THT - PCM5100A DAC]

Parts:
C14, C15, C16, C20: 0.1uF; C_Disc_D5.0mm_W2.5mm_P5.00mm; MPN RDER71H104K0M1H03A; DigiKey 490-9144-1-ND
C17: 10uF; C_Disc_D5.0mm_W2.5mm_P5.00mm; MPN RCER71H106MWM1H03A; DigiKey 490-7518-1-ND
C18, C19: 2.2uF; C_Disc_D5.0mm_W2.5mm_P5.00mm; MPN FG24X7R1H225KRT06; DigiKey 445-173378-1-ND
C21, C22: 2.2nF; C_Disc_D5.0mm_W2.5mm_P5.00mm; MPN FG28C0G1H222JNT06; DigiKey 445-173487-1-ND
R10, R11: 470R; R_Axial_DIN0207_L6.3mm_D2.5mm_P10.16mm_Horizontal; MPN RNMF14FTC470R; DigiKey S470CACT-ND
U10: PCM5100A; TSSOP-20_4.4x6.5mm_P0.65mm_HandSolder_TestPads; MPN PCM5100APWR; DigiKey 296-36705-1-ND

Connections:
+3V3: C14.2, U10.17 (XSMT), U10.20 (DVDD); also elsewhere on the board
AGND: C15.1, C16.1, C17.2, C19.2, C21.1, C22.1, U10.3 (CPGND), U10.9 (AGND); also elsewhere on the board
AVDD: C15.2, C16.2, C17.1, U10.1 (CPVDD), U10.8 (AVDD); also elsewhere on the board
BCK: U10.13 (BCK); also elsewhere on the board
DIN: U10.14 (DIN); also elsewhere on the board
GND: C14.1, C20.2, U10.10 (DEMP), U10.11 (FLT), U10.12 (SCK), U10.16 (FMT), U10.19 (DGND); also elsewhere on the board
LRCK: U10.15 (LRCK); also elsewhere on the board
unnamed: C18.2, U10.4 (CAPM)
unnamed: C18.1, U10.2 (CAPP)
unnamed: C20.1, U10.18 (LDOO)
unnamed: R10.1, U10.6 (OUTL)
unnamed: R11.1, U10.7 (OUTR)
unnamed: C19.1, U10.5 (VNEG)
PGAUDIO_L: C21.2, R10.2; also elsewhere on the board
PGAUDIO_R: C22.2, R11.2; also elsewhere on the board

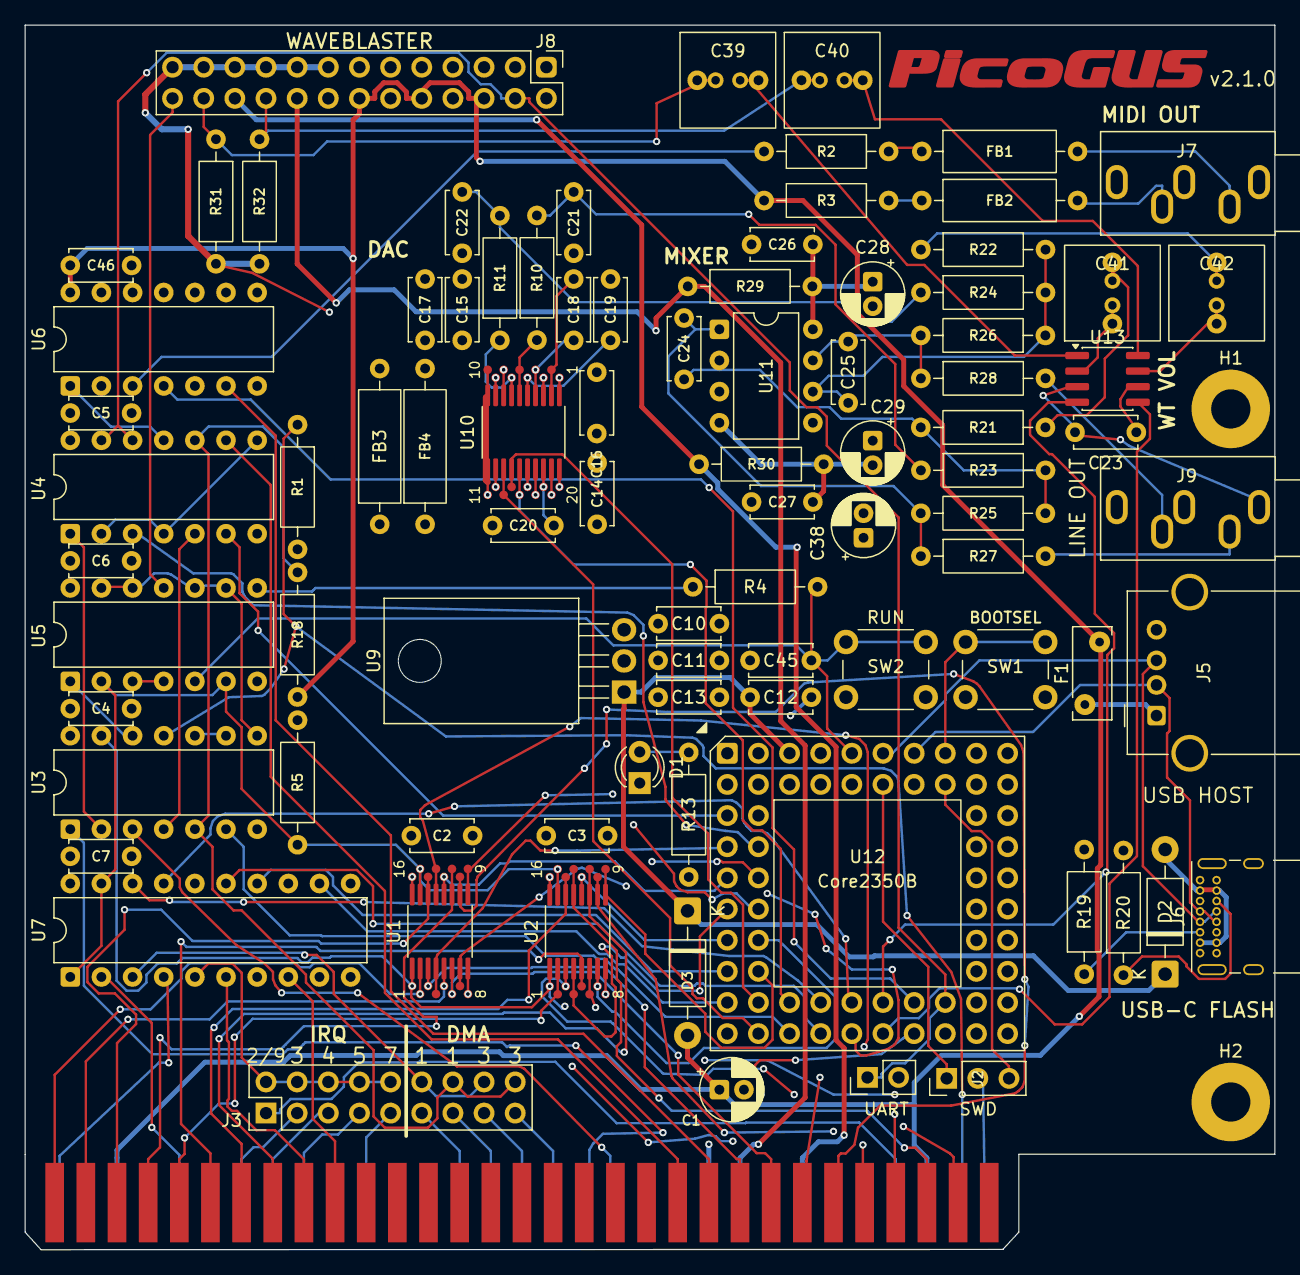
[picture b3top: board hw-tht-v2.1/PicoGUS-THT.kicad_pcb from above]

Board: 4 copper layers, 101.9 x 99.8 mm, 90 parts (0 on the bottom side), 120 nets.
